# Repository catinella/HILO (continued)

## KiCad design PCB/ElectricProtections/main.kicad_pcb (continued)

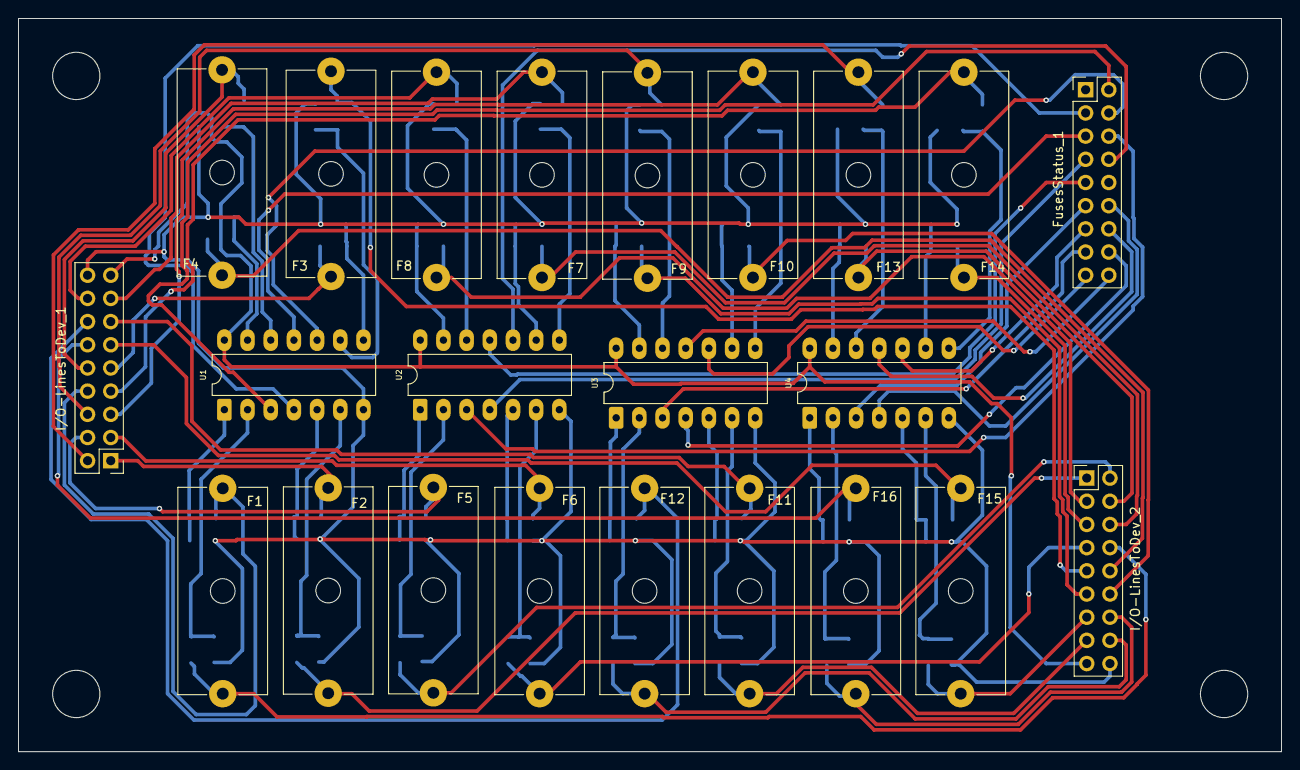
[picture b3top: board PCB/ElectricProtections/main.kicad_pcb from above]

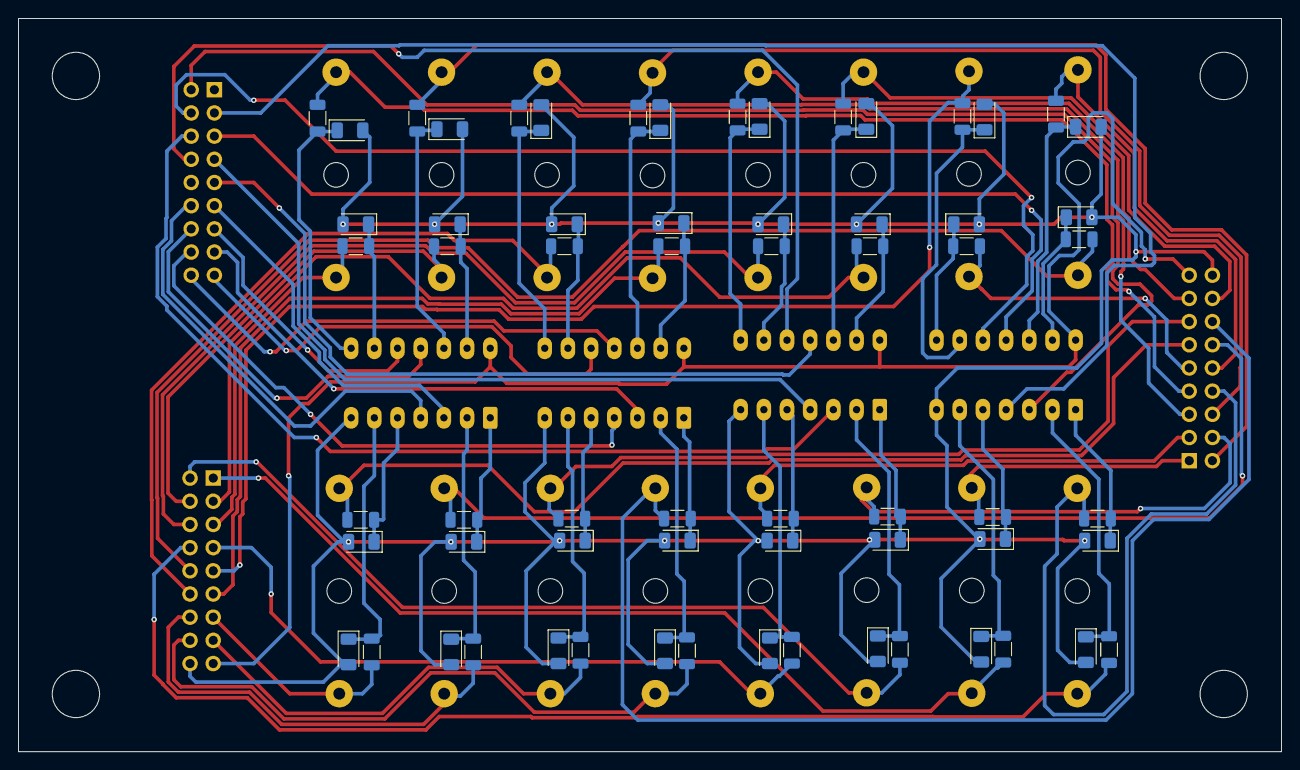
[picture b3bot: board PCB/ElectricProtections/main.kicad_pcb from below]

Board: 2 copper layers, 138.4 x 80.3 mm, 87 parts (64 on the bottom side), 82 nets.

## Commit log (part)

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2025-09-01 Fix: wrong number of memory chips
2025-09-01 Cosmetic change
2025-09-01 New home for all multiplatform code
    wError/include/wError.h -> crossPlatform_code/wError.h
2025-09-03 Updates...
2025-09-03 Uncompleted version
2025-09-04 First completed release
2025-09-05 Fix: missing dep added
2025-09-05 Enhancement: unit test support added
2025-09-05 standard file
2025-09-07 Fix for the executable file linking rule
2025-09-07 Module for the mocked functions
2025-09-07 WERROR_ERRUTEST_NOTYETIMPL symbol added
2025-09-07 Default git-ignore file added
2025-09-10 Small change
    Current-dir has been added to the include-paths list
2025-09-10 testEnd() prototype added
2025-09-10 Fixes for sramManager_write__T1()
2025-09-10 File names changing
2025-09-11 Fix for spi_device_polling_transmit()
    - Wrong conditional statement
2025-09-11 Refactoring: less code fragmentation
    Also the private _spi_initialization() function has been mocked.
2025-09-11 Code refactoring and fixes
    This version function perfectly with foodata smaller then 1MB
2025-09-11 Small change
2025-09-11 Fix for sramManager_write__T1() and small enhancements
    - sramManager_write__T1(): in order to use big data size (8Mb), the data-store has been allolcated in heap memory
    instead stack
    - FOODATA_T1NOI and VERBOSE_UNITTEST symbols definitions have been moved in the Makefile
2025-09-11 Fix for _sram_mcSeqOP(): segmentation fault for illegal ID
2025-09-14 Change: more generic name
2025-09-14 Fix for _spi_initialization()
2025-09-14 Old files ignoring rule added
2025-09-14 IDF_TARGET setting added
    It allows you to avoid to define the target everytime you execute a complete clean procedure
2025-09-14 esp_driver_spi dependence added
2025-09-15 (empty) integration tests added
2025-09-15 A small command to create a symbolic link
2025-09-15 Documentation added
2025-09-15 HILO_MYSSIDNAME and HILO_MYPASSWD symbols management added
2025-09-15 WiFi Access Point creation test
2025-09-15 Test implemented ;-)
2025-09-15 The wifi_init_sta() has been substituted by wifi_connToExtNet()
2025-09-15 WERROR_ERROR_CONFFAILED and WERROR_ERROR_INTFAILURE symbols added
2025-09-15 wifi_intAPstart() added
2025-09-15 The internal AP management proc has been moved in wifi_intAPstart()
2025-09-16 Doc update
2025-09-16 Component for the REST APIs management
2025-09-16 Updates for the new component restApiServer
    There is still a bug with APIs definitions registration
2025-09-17 Update for restApiServer_configure() prototype
2025-09-17 Fixews for log messages
2025-09-26 Preliminary version
    At the moment I have not yet bought the right dev-kit, so I am doing some test with an ARM cortex-M0 MCU.
    However, I wrote a Makefile for the firmware building that function very well.
    (special thanks to Chat-GPT for the support on the conversion from STM building chain to Makefile)
2025-09-29 Changes: new main scheme
2025-09-29 The process' documentation has been moved to the README file
2025-09-30 Enhancement: multi-target firmrware building
    Now, you can build the firmware for different STM targets without change the Makefile
2025-09-30 Fix for linker rule, doc added, and enhancements
2025-10-21 New JSON messages for the test-configuration Rest-API
    The original idea was to allow the test-client to send all bits-configurations trought the Rest-API. But it is not a good idea,
    because the ESP32 has no enough memory to store temporary those data.
    So, the new idea is to send the test data in higher level description JSON-messages and to let the ESP32 to convert the smaller
    data version in the bits-sequences. In this way ESP32 doesn't need to store data in its internal RAM.
2025-10-24 WERROR_ERROR_ITEMNOTFOUND symbol added
2025-10-25 sram_manager module has been disabled
    sram_manager module manage the SRAMs pool as a big single fast fifo. In the previouse architecture the test-client software
    proveide test-data in raw way (bit per bit) ready to be used by the HILO_engine's MCU. But, because the HILO_interface's MCU
    (ESP32) has not enough memory to store all (MBytes) data, the new solution is to provide just data-set definition, and let
    the MCU to generate the raw data. For this reason the sram_manager module is no more useful :-(
    I hope to port this module to the HILO-engine (STM32-M4) architecture.
2025-10-25 Empty-function definitions added
2025-10-25 English language errors fixed
2025-10-25 Building tools to include multiple header files
2025-10-27 Wrong help message fixed
2025-10-27 Building process created files ignoring
2025-10-27 Wrong wError symbols fixed
2025-10-29 Sybols added
    WERROR_ERROR_INTERNALS
    WERROR_ERROR_ILLEGALSYNTAX
2025-10-30 Mocked version in progress
2025-10-30 MOCK symbol management added
2025-10-30 Small change y() --> x##__##y()
2025-11-01 Common utilities module
2025-11-01 ASSERT_TRUE() macro added
2025-11-01 Rules update for the new utilities.o file
2025-11-01 Fix for strupr()
2025-11-01 APIs arguments change
    Because the module reads JSON messages but it does not modify them, the functions' argument have been changed from "cJSON *var" to "const cJSON *var"
2025-11-01 Standard header-comment added
2025-11-01 Many changes
    - _setParams() added
    - testDataCompiler_generate() rewritten
    - testDataCompiler_setParams() removed
    - testDataCompiler_getParams() modifyied
2025-11-01 Fixes and new test added
    - jsonMsg text fixed
    - TEST(T5): wrong parsed text fixed
    - TEST(T6): added
2025-11-02 math.h lib linking added
2025-11-02 Fixes for the foo JSON messages
2025-11-02 Enhancement for testData_number_check()
2025-11-02 Fix for NUM_jsonMsg JSON message
2025-11-03 Small fix for the file's comments
2025-11-03 Enhancements for all T2__f(x) .. T4__f(x) tests
2025-11-03 standard README file
2025-11-04 New rules for dataViewer file building
2025-11-04 Enhancement: Vertical lines for time references
2025-11-07 Markup down coded file
2025-11-07 README --> README.md
2025-11-07 Local image added and fixes for table
2025-11-07 Another fix for MD
2025-11-07 Image as document title
2025-11-08 Nicer banner
    (Special thank to Chat-GPT)
2025-11-08 Links added
2025-11-12 MOCK symbol definition added to all utests building process
2025-11-12 Refactoring
    utest__testDataCompiler.c has been splitted in specialized files
2025-11-12 Fix for testData_fixedTimePeriod_generate()
    Wrong bits shift command fixed
2025-11-12 T3::testDataCompiler_generate() added
2025-11-13 Experimental files
    About the MD files (README usually), it would be nice to generate the diagrams by a text language. So, I am trying to use
    plantUML. It is a great app but it looks like full of bugs, so I don't know if it will be usable. But it is still a great
    project
2025-11-14 Rule for Makefile's configuration file ignoring added
2025-11-15 Enhancement
2025-11-15 Small Henancement
2025-11-19 PlantUML integration test for GitHUB
2025-11-19 Rollback
2025-11-19 Fix: interactive-mode replace realtime-mode
2025-11-20 Small enhancement
2025-11-21 "2.3 Communication channel" section added
    In this section I explain why I used TCP/IP connection instead the usual USB/RS485/RS232/CAN... bus
2025-11-24 Fixes for testDataCompiler_write()
    - _getPin(), _setPin(), _swapPin() private functions added
    - testDataCompiler_write() has been almost comletely rewritten
2025-11-24 Update for tdcLogicOperator_t
2025-11-25 New implementation and fixes
    - Enhancements for testData_number_check(): more deep checks for JSON
    - _isNotUsedPin() private function added
    - New implementation for testData_number_generate()
2025-11-25 New tests added to achieve higher code coverrage
2025-11-25 Small cosmetic change
2025-11-25 New test for squareWave sub-module
2025-11-25 "freq" conf-field fixed in JSON messages
    5 --> 50: 50 = 5Khz
2025-11-26 Numeric index added on the timeline
2025-11-26 Fixes for testData_squareWave_generate()
    100% tested version
2025-11-27 Test client
2025-11-29 Refactoring
2025-11-30 conf.pri configuration file added
2025-12-07 New widget created with QT-Designer
2025-12-08 New widget used by all HILO's tools
    This widget is used by all the others to connect themselves to the HILO's input/output pins
2025-12-08 standard header comment added
2025-12-09 Aesthetic adjustments
2025-12-10 Single pin widget
2025-12-10 Licence document link/position fixed
2025-12-10 LGPL-3.0 licence added
2025-12-10 ...small fix
2025-12-12 Wrong comment for typing error fixed
2025-12-12 Dependence added
    libPinWidget.a file must be already built
2025-12-12 Dependence check added
    libPinWidget.a file must be already built
2025-12-12 Implementation
2025-12-12 Small fix for ToolWidget's constructor
2025-12-13 Many fixes
    The graphic component functions very well, but
    - Link cannot be modified
    - Bit changes are not notified to the DUT's PinSet
2025-12-13 Layout documentation added
2025-12-14 Small refactoring
    The addConnection() and terminalCenter() methods was used just internally. So I moved them in the private set
2025-12-15 pinConnection class added
    It provides a better reppresentation of the pins-link data type
2025-12-15 Updates to use the new PinConnection class
    It has been a good refactoring ;-)
2025-12-16 onTerminalValueChanged() slot prototype added
2025-12-17 Enhancement: every pin must be set as DUT's side or Tool's side one
    - m_side property added as private one
    - getSide() method added
2025-12-17 Unwanted connection between pin of the same side, has been fixed
    - changes for pinConnection::addItem() method
2025-12-17 Updates to the new PinStripe version
    Changes for the PinStripe new constructor
2025-12-18 Test's documentation added
    Whole test workflow diagram
2025-12-18 Enhancement for the TestWidget's constructor
    - Unuseful code removed
2025-12-18 Files ordering
2025-12-19 Documentation fixed and window backgroound color added
2025-12-19 mbiguos var name changed
2025-12-19 Bug report removed
2025-12-21 Updates for the new PinStrip's feature
    You can move the object in drag-drop way
2025-12-27 Fix for mouseReleaseEvent(): unuseful update() call removed
2025-12-27 Enhancement for the Object constructor
    - in the dragging signal handler, a new feature has been added: the pin connections re-drawing call after the PinStripe movement
2025-12-27 Images and diagrams have moved to their local folder
2025-12-27 Movement feature schema added
2025-12-28 Fix for the objects constructor method
    Wrong graphic behavior when the main-window size change
2025-12-28 Doc added
2025-12-29 Small fixes
    Unuseful "FORMS" keyword definition has been deleted
    "INCLUDEPATH" keuword added for PinWidget.h file
2025-12-29 Dependences added and other fixes
2025-12-29 PinStrip widget added (uncompleted version)
2025-12-29 Small fix for normalize(): wrong returned value
2025-12-29 MyWindow class was an unusefull one. It has been removed
    MyWindow class implementation has been moved into the test.cpp file
2025-12-29 Widget's size reduction
2025-12-29 Changes
    - uneseful code removed by ../KeypadWidget.h
    - emitted ok-signal prings an integer number instesd a text
    - display content is now tested before the ok-signal is emitted
2025-12-30 Syntactic sugar
2025-12-30 KeypadWidget movement enabling
2026-01-09 Usual git-ignore file
2026-01-09 Updates: DragController engine used
    - The dragging management has procedure has been substituted by DragController engine
2026-01-09 Updates for the new PinStripe release
2026-01-10 Missing INCLUDE path fixed
2026-01-10 Propcedure to override vars' content with environment vars one
    [!] Because it requires to modify global vars. It CANNOT be converted in a normal function
    (QMake is not a good tool!!)
2026-01-10 Updates
    This version uses the QMake libraries.
2026-01-12 Updates for the new KeypadWidget implementation
2026-01-13 Update: cleanall rule defined in external file
2026-01-13 cleanall rule centralization
